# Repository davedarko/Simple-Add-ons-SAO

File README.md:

# Simple-Add-ons-SAO
Hardware Conference Badges tend to turn very complex, so to allow people to add bling and memes to their badge, the SAO (then shitty add-on) standard was developed. It started as a 2x2 header with two power pins and two I2C pins for data and a clock signal. Let me introduce you to the standard and show you what can be achieved. This is one of my favorite things to design, as they can be nice little gifts and inspires a lot of people for future years to also design and gift some. 

They are perfect gifts and spark joy!

Find all of my ~~shitty~~ simple add-ons in this repository. Plus some badges that were never converted to SAO but they still blink and everything.

## The current header - V1.69bis
The header was expanded to a 2x3 ISP connector later. Looking at the simple add-on, this is the layout.

## Designs in this repository

|Badge Name| Type | Eagle | Kicad | Description |
|----------|------|-------|-------|-------------|
| Ghibli/Soot Sprites | SAO | yes | - | A susuwatari simple add-on |
| LECCO postcard  | SAO | yes | - | Reminder token for a good time at Hackaday Europe 2026 in Lecco, Italy |
| Han SAOlo in carbonyte  | SAO | - | yes | work in progress, Attiny202 with RGB LEDs https://hackaday.io/project/197803-han-saolo|
| COVID-19 badge | SAO | - | yes | blinks with the help of a 555 timer on the back https://hackaday.io/project/187615-covid-19-sao-simple-add-on |
| "Hello my name is"  | SAO | - | yes | some blinks, some no https://hackaday.io/project/197693-hello-my-name-is-sao |
| MrAnderson  | SAO | - | yes | work in progress, hommage to Andy Anderson |
| Vendetta badge | SAO | - | yes | "remember, remember the 5th of November" - or anything else with the help of the little EEPROM on the back of this badge |
| Mr. Robot | SAO | yes | yes | with Attiny speaker https://hackaday.io/project/168037-mr-robot-shitty-addon |
| Penghito Poco | SAO | yes | - | small penghicorn badge |
| Do Or Donut | SAO | yes | - |  LED sprinkle matrix https://hackaday.io/project/168597-do-or-donut-sao |
| Knight Rider badge | SAO / pin | yes | yes | K.I.T.T. with animations thanks to an Attiny13 https://hackaday.io/project/25944-kitt-knight-rider-badgebrooch |
| sloth badge | pin | yes | - | inspired by some cute pimoroni pins, a sloth badge was formed https://hackaday.io/project/28330-sloth-badge |
| flux capacitor | pin | yes | - | with animations thanks to an Attiny13, the flux is flowing https://hackaday.io/project/25898-flux-capacitor-trinket|
| retro spacehuhn badge | pin | yes | - | RGB LED eyes on an olg Spacehuhn logo, with markers used for multicolor PCBs https://hackaday.io/project/33886-spacehuhn-badge |
| library stick  | other | yes | - | show off all your simple add-ons |

## Further designs

|Badge Name| Type | Eagle | Kicad | Description |
|----------|------|-------|-------|-------------|
| YoDawgSAO | SAO| - | yes| I heard you like badges on your badges? Here have some badges for your badges for your badges! https://github.com/davedarko/YoDawgSAO |
| T.A.R.S. | SAO| - | yes| Probably my most complex design, a small TARS with display and RP2040 https://github.com/davedarko/TARS-SAO |

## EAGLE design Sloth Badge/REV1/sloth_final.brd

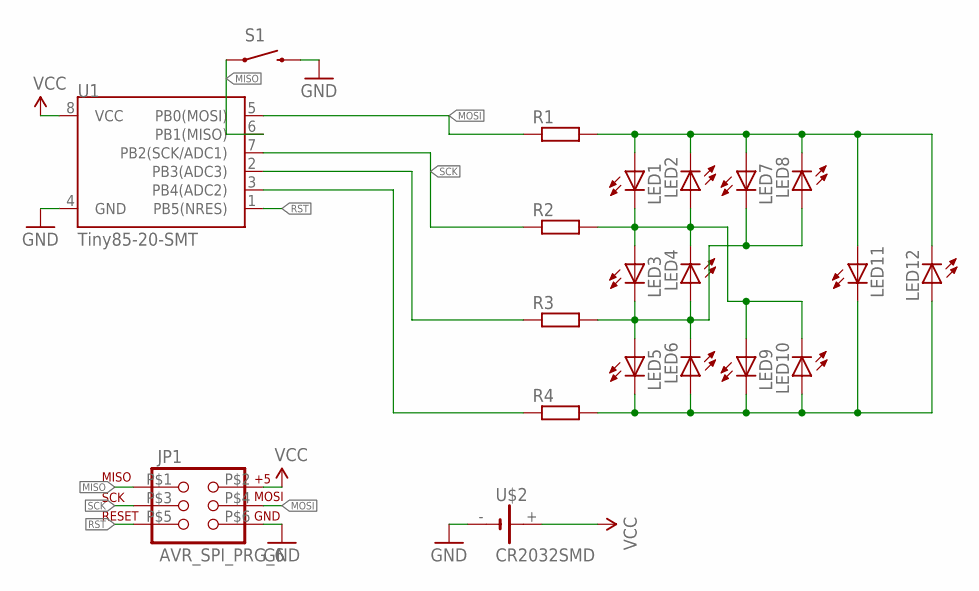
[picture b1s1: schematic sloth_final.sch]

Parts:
JP1: AVR_SPI_PRG_6; 2X3_SMD_PAD
LED1, LED2, LED3, LED4, LED5, LED6, LED7, LED8, LED9, LED10, LED11, LED12: LEDCHIP-LED0805; CHIP-LED0805
R1, R2, R3, R4: R-EU_R0805; R0805
S1: SWITCH-MOMENTARY-2-SMD-1101NE; TACTILE-SWITCH-1101NE
U1: Tiny85-20-SMT; SO08-EIAJ
U$2: CR2032SMD

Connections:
GND: JP1.P$6 (6), S1.P$2 (2), U1.4 (GND), U$2.-
MISO: JP1.P$1 (1), S1.P$1 (1), U1.6 (PB1(MISO))
MOSI: JP1.P$4 (4), R1.1, U1.5 (PB0(MOSI))
unnamed: R4.1, U1.3 (PB4(ADC2))
unnamed: LED5.C, LED6.A, LED9.C, LED10.A, LED11.C, LED12.A, R4.2
unnamed: LED1.A, LED2.C, LED7.A, LED8.C, LED11.A, LED12.C, R1.2
unnamed: LED1.C, LED2.A, LED3.A, LED4.C, LED9.A, LED10.C, R2.2
unnamed: LED3.C, LED4.A, LED5.A, LED6.C, LED7.C, LED8.A, R3.2
PB3: R3.1, U1.2 (PB3(ADC3))
RST: JP1.P$5 (5), U1.1 (PB5(NRES))
SCK: JP1.P$3 (3), R2.1, U1.7 (PB2(SCK/ADC1))
VCC: JP1.P$2 (2), U1.8 (VCC), U$2.+

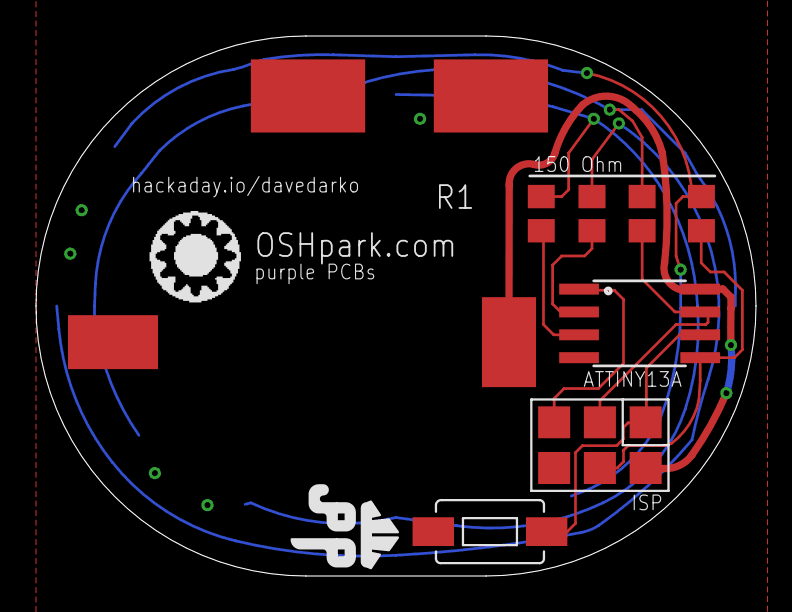
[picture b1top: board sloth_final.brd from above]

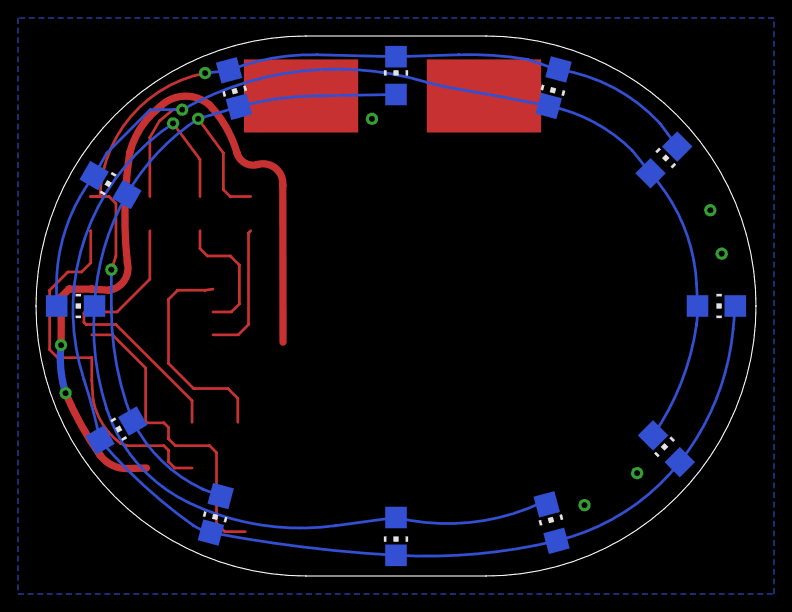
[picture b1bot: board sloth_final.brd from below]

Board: 2 copper layers, 40.0 x 30.0 mm, 22 parts (12 on the bottom side), 12 nets.

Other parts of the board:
U$1: DAVEDARKO2_LOGO
U$3: OSHPARK_LOGO

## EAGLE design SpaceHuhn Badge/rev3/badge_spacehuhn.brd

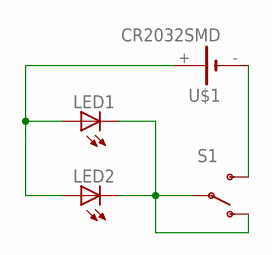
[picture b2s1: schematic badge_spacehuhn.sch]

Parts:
LED1, LED2: LED5MM
S1: SWITCH-SPDT-SMD-A; SWITCH-SPST-SMD-A
U$1: CR2032SMD

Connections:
GND: LED1.K (C), LED2.K (C), S1.1 (O), S1.2
unnamed: S1.3 (S), U$1.-
VCC: LED1.A, LED2.A, U$1.+

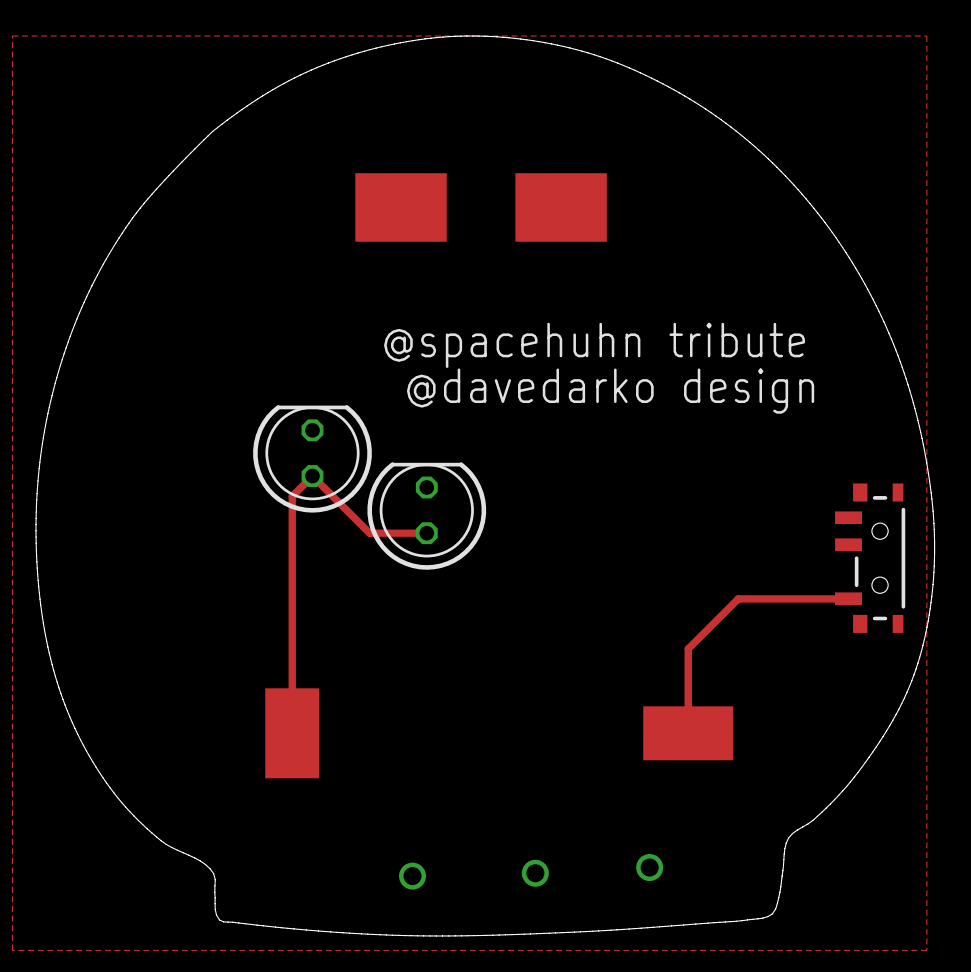
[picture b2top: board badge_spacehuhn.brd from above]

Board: 2 copper layers, 49.9 x 50.0 mm, 5 parts (0 on the bottom side), 3 nets.

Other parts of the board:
U$2: DAVEDARKO_GOLD

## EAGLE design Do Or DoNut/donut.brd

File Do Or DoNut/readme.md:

# Do or Donut SAO
donut shaped LED matrix SAO

## idea
Use an IS31FL3731 to control 8 x 18 LEDs wrapped around a donut shaped PCB, sprinkled with LEDs.

## Links 
- Hackaday IO project page  
[https://hackaday.io/project/168597-do-or-donut-sao](https://hackaday.io/project/168597-do-or-donut-sao)

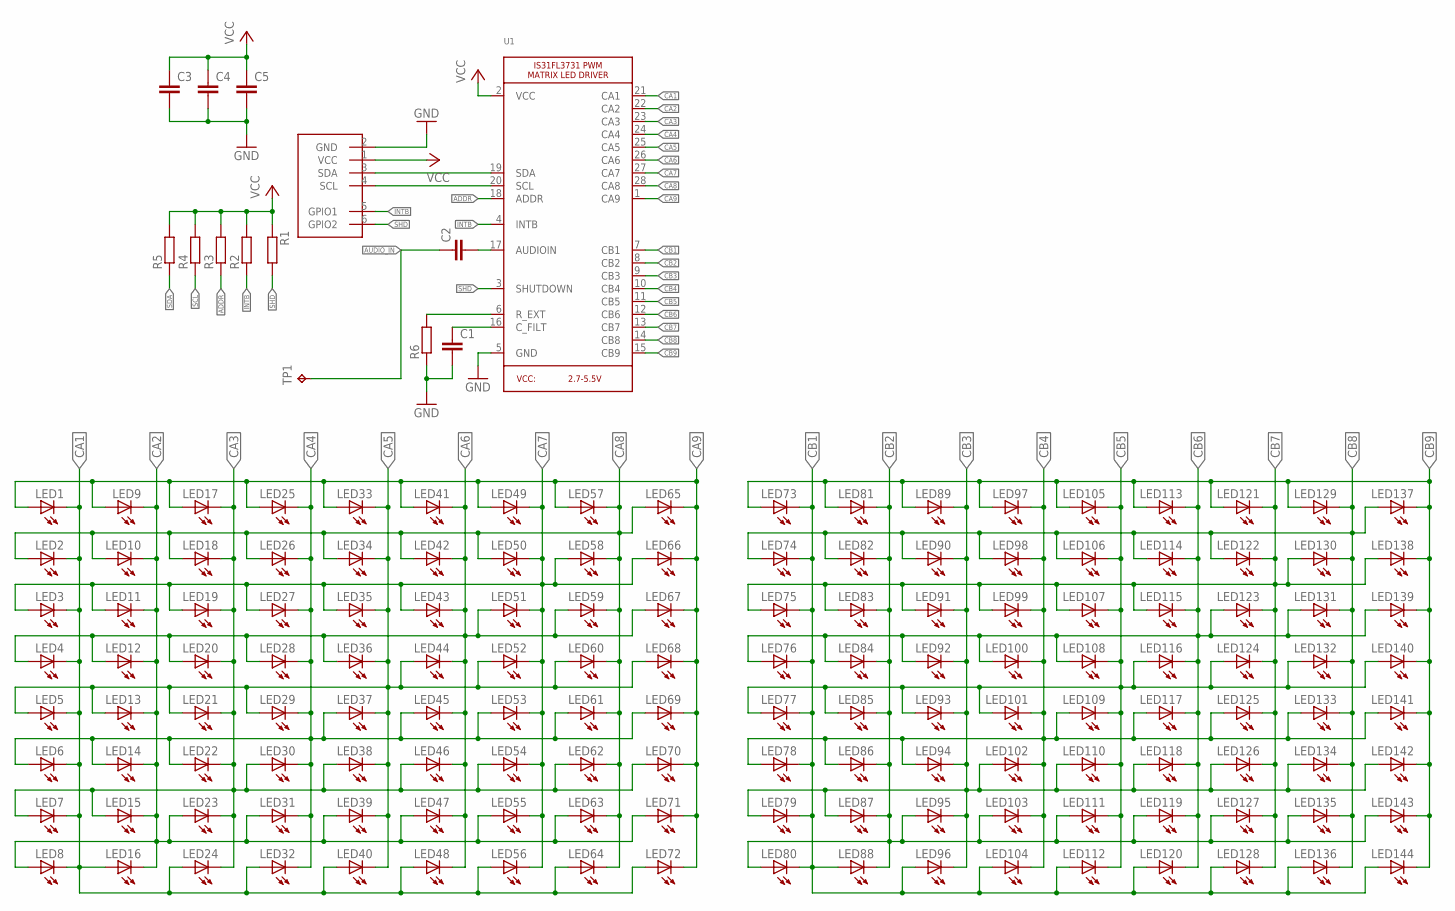
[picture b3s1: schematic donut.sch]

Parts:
C1, C2, C3, C4, C5: C-EUC0603; C0603
LED1, LED2, LED3, LED4, LED5, LED6, LED7, LED8, LED9, LED10, LED11, LED12, LED13, LED14, LED15, LED16, LED17, LED18, LED19, LED20, LED21, LED22, LED23, LED24, LED25, LED26, LED27, LED28, LED29, LED30, LED31, LED32, LED33, LED34, LED35, LED36, LED37, LED38, LED39, LED40, LED41, LED42, LED43, LED44, LED45, LED46, LED47, LED48, LED49, LED50, LED51, LED52, LED53, LED54, LED55, LED56, LED57, LED58, LED59, LED60, LED61, LED62, LED63, LED64, LED65, LED66, LED67, LED68, LED69, LED70, LED71, LED72, LED73, LED74, LED75, LED76, LED77, LED78, LED79, LED80, LED81, LED82, LED83, LED84, LED85, LED86, LED87, LED88, LED89, LED90, LED91, LED92, LED93, LED94, LED95, LED96, LED97, LED98, LED99, LED100, LED101, LED102, LED103, LED104, LED105, LED106, LED107, LED108, LED109, LED110, LED111, LED112, LED113, LED114, LED115, LED116, LED117, LED118, LED119, LED120, LED121, LED122, LED123, LED124, LED125, LED126, LED127, LED128, LED129, LED130, LED131, LED132, LED133, LED134, LED135, LED136, LED137, LED138, LED139, LED140, LED141, LED142, LED143, LED144: LEDCHIP-LED0603; CHIP-LED0603
R1, R2, R3, R4, R5, R6: R-EU_R0603; R0603
TP1: TPB1,27; B1,27
U1: IS31FL3731SSOP; SSOP28DB
U$1: SAO-SHITTY-ADDONBADGE; 2X3-SHROUDED

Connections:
ADDR: R3.1, U1.18 (ADDR)
AIN: C2.2, U1.17 (AUDIOIN)
AUDIO_IN: C2.1, TP1.TP
CA1: LED1.C, LED2.C, LED3.C, LED4.C, LED5.C, LED6.C, LED7.C, LED8.C, LED16.A, LED24.A, LED32.A, LED40.A, LED48.A, LED56.A, LED64.A, LED72.A, U1.21 (CA1)
CA2: LED8.A, LED9.C, LED10.C, LED11.C, LED12.C, LED13.C, LED14.C, LED15.C, LED16.C, LED23.A, LED31.A, LED39.A, LED47.A, LED55.A, LED63.A, LED71.A, U1.22 (CA2)
CA3: LED7.A, LED15.A, LED17.C, LED18.C, LED19.C, LED20.C, LED21.C, LED22.C, LED23.C, LED24.C, LED30.A, LED38.A, LED46.A, LED54.A, LED62.A, LED70.A, U1.23 (CA3)
CA4: LED6.A, LED14.A, LED22.A, LED25.C, LED26.C, LED27.C, LED28.C, LED29.C, LED30.C, LED31.C, LED32.C, LED37.A, LED45.A, LED53.A, LED61.A, LED69.A, U1.24 (CA4)
CA5: LED5.A, LED13.A, LED21.A, LED29.A, LED33.C, LED34.C, LED35.C, LED36.C, LED37.C, LED38.C, LED39.C, LED40.C, LED44.A, LED52.A, LED60.A, LED68.A, U1.25 (CA5)
CA6: LED4.A, LED12.A, LED20.A, LED28.A, LED36.A, LED41.C, LED42.C, LED43.C, LED44.C, LED45.C, LED46.C, LED47.C, LED48.C, LED51.A, LED59.A, LED67.A, U1.26 (CA6)
CA7: LED3.A, LED11.A, LED19.A, LED27.A, LED35.A, LED43.A, LED49.C, LED50.C, LED51.C, LED52.C, LED53.C, LED54.C, LED55.C, LED56.C, LED58.A, LED66.A, U1.27 (CA7)
CA8: LED2.A, LED10.A, LED18.A, LED26.A, LED34.A, LED42.A, LED50.A, LED57.C, LED58.C, LED59.C, LED60.C, LED61.C, LED62.C, LED63.C, LED64.C, LED65.A, U1.28 (CA8)
CA9: LED1.A, LED9.A, LED17.A, LED25.A, LED33.A, LED41.A, LED49.A, LED57.A, LED65.C, LED66.C, LED67.C, LED68.C, LED69.C, LED70.C, LED71.C, LED72.C, U1.1 (CA9)
CB1: LED73.C, LED74.C, LED75.C, LED76.C, LED77.C, LED78.C, LED79.C, LED80.C, LED88.A, LED96.A, LED104.A, LED112.A, LED120.A, LED128.A, LED136.A, LED144.A, U1.7 (CB1)
CB2: LED80.A, LED81.C, LED82.C, LED83.C, LED84.C, LED85.C, LED86.C, LED87.C, LED88.C, LED95.A, LED103.A, LED111.A, LED119.A, LED127.A, LED135.A, LED143.A, U1.8 (CB2)
CB3: LED79.A, LED87.A, LED89.C, LED90.C, LED91.C, LED92.C, LED93.C, LED94.C, LED95.C, LED96.C, LED102.A, LED110.A, LED118.A, LED126.A, LED134.A, LED142.A, U1.9 (CB3)
CB4: LED78.A, LED86.A, LED94.A, LED97.C, LED98.C, LED99.C, LED100.C, LED101.C, LED102.C, LED103.C, LED104.C, LED109.A, LED117.A, LED125.A, LED133.A, LED141.A, U1.10 (CB4)
CB5: LED77.A, LED85.A, LED93.A, LED101.A, LED105.C, LED106.C, LED107.C, LED108.C, LED109.C, LED110.C, LED111.C, LED112.C, LED116.A, LED124.A, LED132.A, LED140.A, U1.11 (CB5)
CB6: LED76.A, LED84.A, LED92.A, LED100.A, LED108.A, LED113.C, LED114.C, LED115.C, LED116.C, LED117.C, LED118.C, LED119.C, LED120.C, LED123.A, LED131.A, LED139.A, U1.12 (CB6)
CB7: LED75.A, LED83.A, LED91.A, LED99.A, LED107.A, LED115.A, LED121.C, LED122.C, LED123.C, LED124.C, LED125.C, LED126.C, LED127.C, LED128.C, LED130.A, LED138.A, U1.13 (CB7)
CB8: LED74.A, LED82.A, LED90.A, LED98.A, LED106.A, LED114.A, LED122.A, LED129.C, LED130.C, LED131.C, LED132.C, LED133.C, LED134.C, LED135.C, LED136.C, LED137.A, U1.14 (CB8)
CB9: LED73.A, LED81.A, LED89.A, LED97.A, LED105.A, LED113.A, LED121.A, LED129.A, LED137.C, LED138.C, LED139.C, LED140.C, LED141.C, LED142.C, LED143.C, LED144.C, U1.15 (CB9)
GND: C1.2, C3.2, C4.2, C5.2, R6.1, U1.5 (GND), U$1.2 (GND)
INTB: R2.1, U1.4 (INTB), U$1.5 (GPIO1)
unnamed: R6.2, U1.6 (R_EXT)
unnamed: C1.1, U1.16 (C_FILT)
SCL: R4.1, U1.20 (SCL), U$1.4 (SCL)
SDA: R5.1, U1.19 (SDA), U$1.3 (SDA)
SHD: R1.2, U1.3 (SHUTDOWN), U$1.6 (GPIO2)
VCC: C3.1, C4.1, C5.1, R1.1, R2.2, R3.2, R4.2, R5.2, U1.2 (VCC), U$1.1 (VCC)

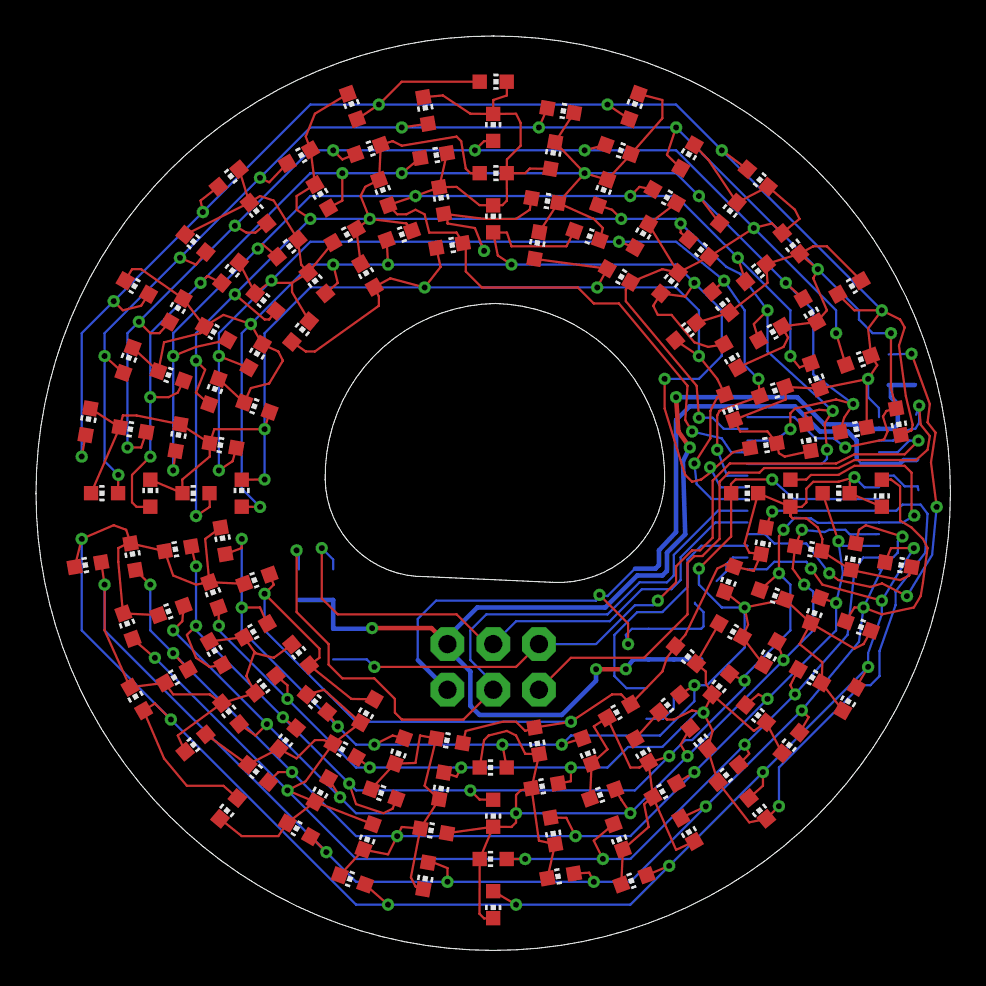
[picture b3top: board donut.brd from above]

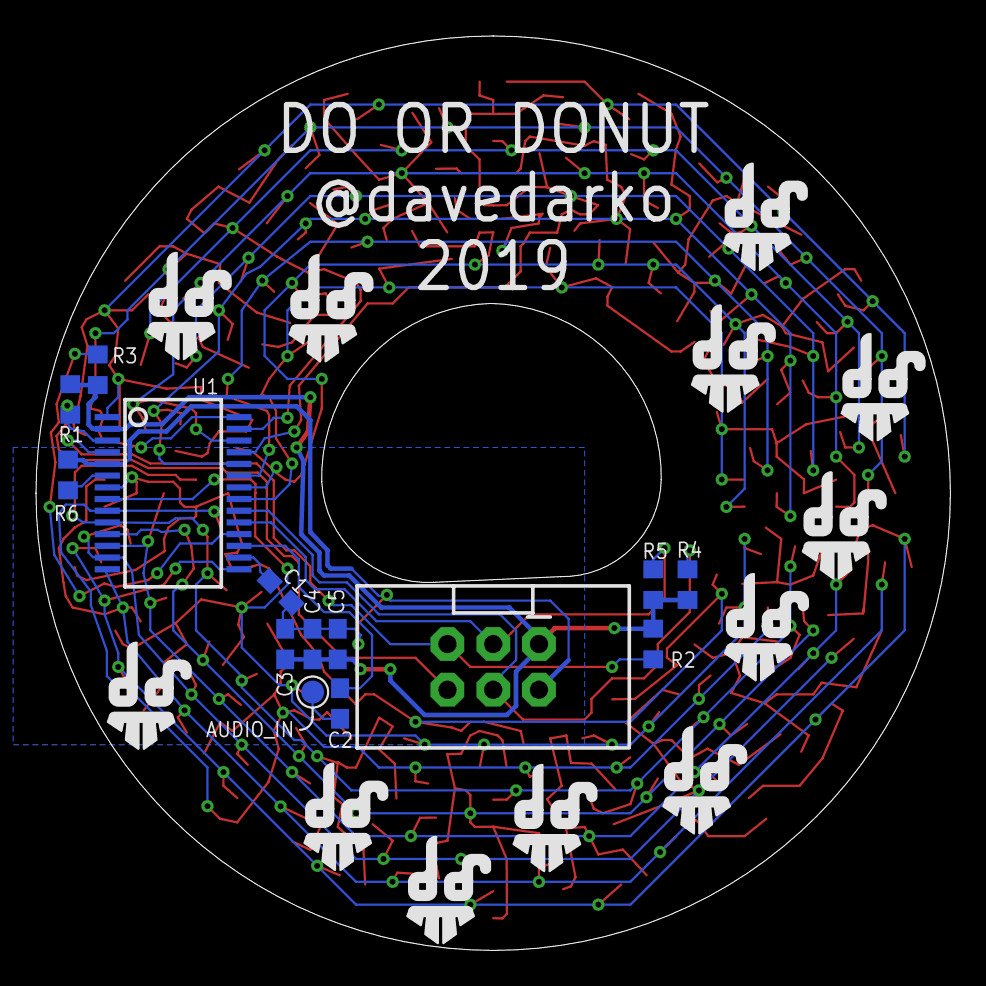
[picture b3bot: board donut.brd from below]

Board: 2 copper layers, 50.8 x 50.8 mm, 170 parts (26 on the bottom side), 29 nets.

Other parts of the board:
U$2, U$3, U$4, U$5, U$6, U$7, U$8, U$9, U$10, U$11, U$12, U$13: DAVEDARKO2_LOGO

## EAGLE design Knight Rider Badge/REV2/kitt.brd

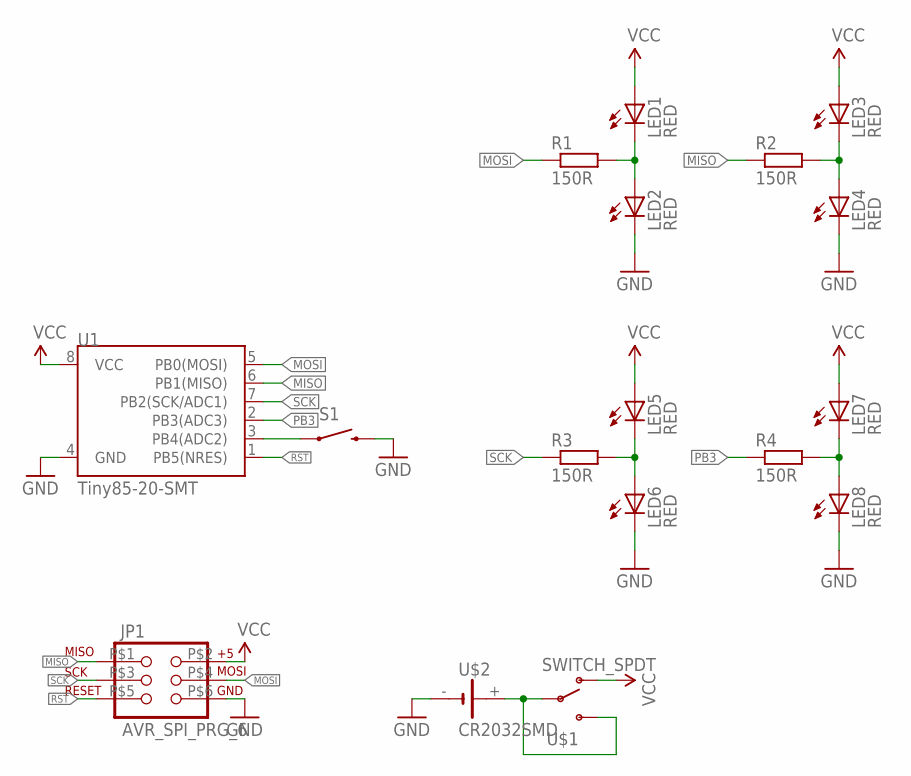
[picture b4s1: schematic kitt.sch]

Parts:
JP1: AVR_SPI_PRG_6; 2X3_SMD_PAD
LED1, LED2, LED3, LED4, LED5, LED6, LED7, LED8: RED; CHIP-LED0805
R1, R2, R3, R4: 150R; M0805
S1: SWITCH-MOMENTARY-2-SMD-1101NE; TACTILE-SWITCH-1101NE
U1: Tiny85-20-SMT; SO08-EIAJ
U$1: SWITCH_SPDT; KPS-1290
U$2: CR2032SMD

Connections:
GND: JP1.P$6 (6), LED2.C, LED4.C, LED6.C, LED8.C, S1.P$2 (2), U1.4 (GND), U$2.-
MISO: JP1.P$1 (1), R2.1, U1.6 (PB1(MISO))
MOSI: JP1.P$4 (4), R1.1, U1.5 (PB0(MOSI))
unnamed: S1.P$1 (1), U1.3 (PB4(ADC2))
unnamed: LED1.C, LED2.A, R1.2
unnamed: U$1.P, U$1.S, U$2.+
unnamed: LED3.C, LED4.A, R2.2
unnamed: LED5.C, LED6.A, R3.2
unnamed: LED7.C, LED8.A, R4.2
PB3: R4.1, U1.2 (PB3(ADC3))
RST: JP1.P$5 (5), U1.1 (PB5(NRES))
SCK: JP1.P$3 (3), R3.1, U1.7 (PB2(SCK/ADC1))
VCC: JP1.P$2 (2), LED1.A, LED3.A, LED5.A, LED7.A, U1.8 (VCC), U$1.O

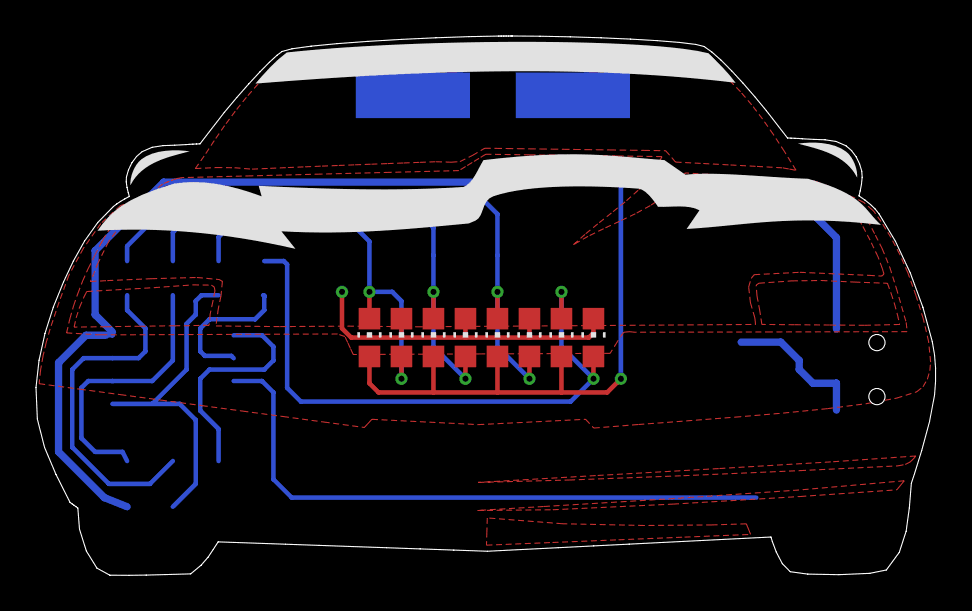
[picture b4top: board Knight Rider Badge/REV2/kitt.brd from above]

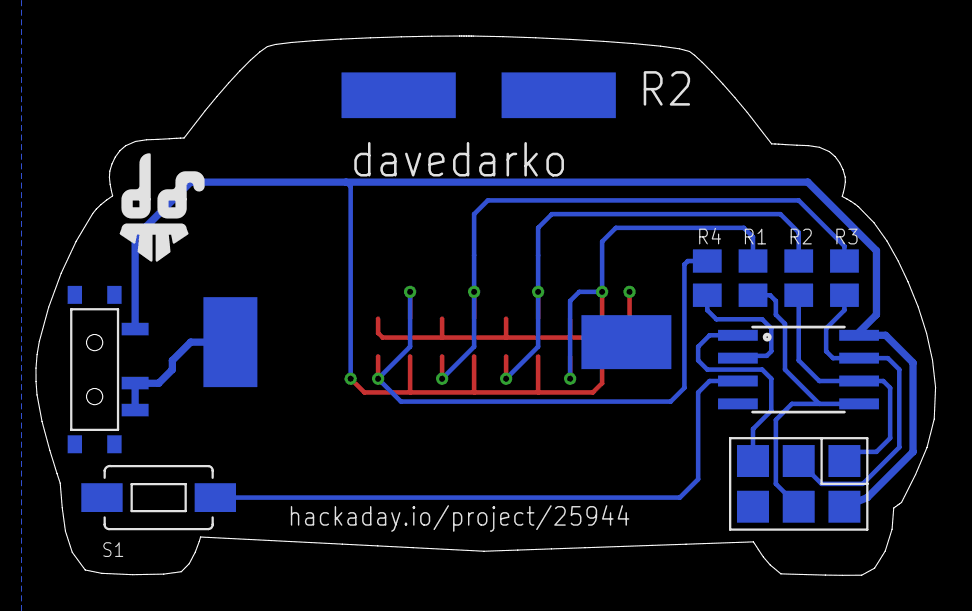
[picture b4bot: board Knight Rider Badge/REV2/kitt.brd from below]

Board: 2 copper layers, 50.0 x 30.0 mm, 18 parts (10 on the bottom side), 13 nets.

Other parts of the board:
U$3: DAVEDARKO2_LOGO

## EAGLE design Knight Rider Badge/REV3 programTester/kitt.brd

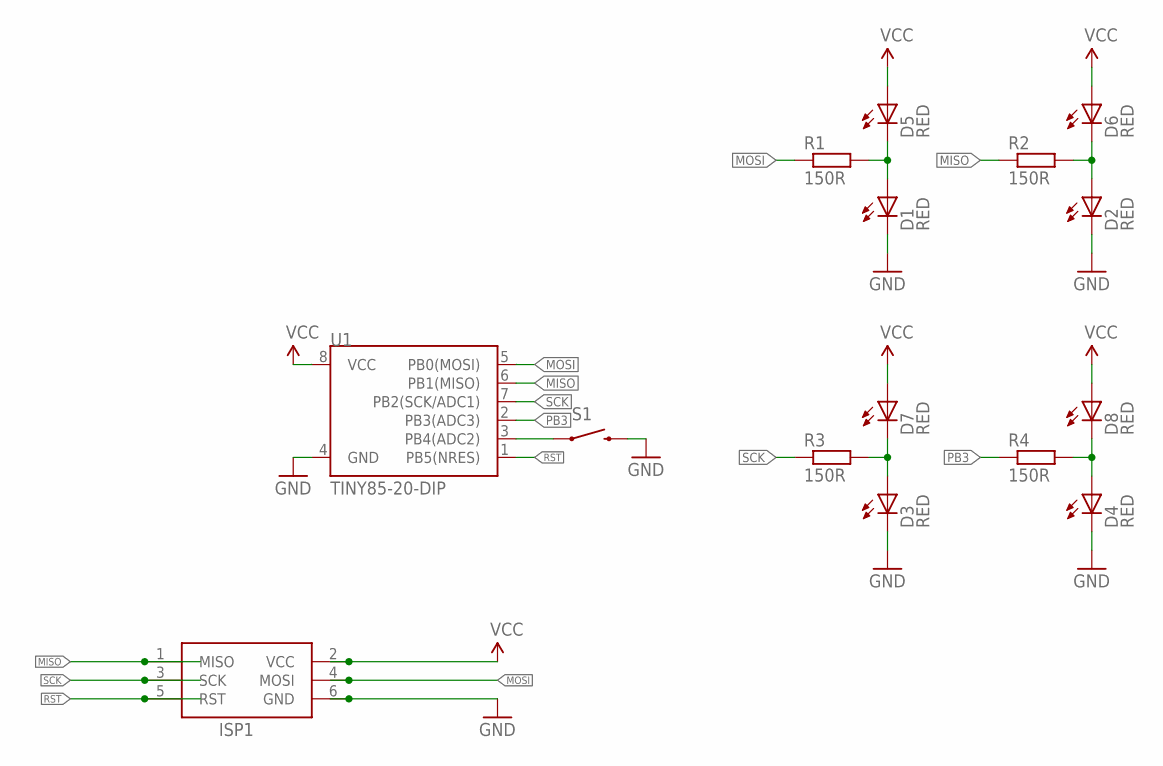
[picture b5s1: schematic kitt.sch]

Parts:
D1, D2, D3, D4, D5, D6, D7, D8: RED; CHIP-LED0805
ISP1: AVRISP-BOX
R1, R2, R3, R4: 150R; M0805
S1: SWITCH-MOMENTARY-2PTH; TACTILE-PTH
U1: TINY85-20-DIP; DIP08

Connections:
GND: D1.C, D2.C, D3.C, D4.C, ISP1.6 (GND), S1.3 (2), U1.4 (GND)
MISO: ISP1.1 (MISO), R2.1, U1.6 (PB1(MISO))
MOSI: ISP1.4 (MOSI), R1.1, U1.5 (PB0(MOSI))
unnamed: S1.1, U1.3 (PB4(ADC2))
unnamed: D1.A, D5.C, R1.2
unnamed: D2.A, D6.C, R2.2
unnamed: D3.A, D7.C, R3.2
unnamed: D4.A, D8.C, R4.2
PB3: R4.1, U1.2 (PB3(ADC3))
RST: ISP1.5 (RST), U1.1 (PB5(NRES))
SCK: ISP1.3 (SCK), R3.1, U1.7 (PB2(SCK/ADC1))
VCC: D5.A, D6.A, D7.A, D8.A, ISP1.2 (VCC), U1.8 (VCC)

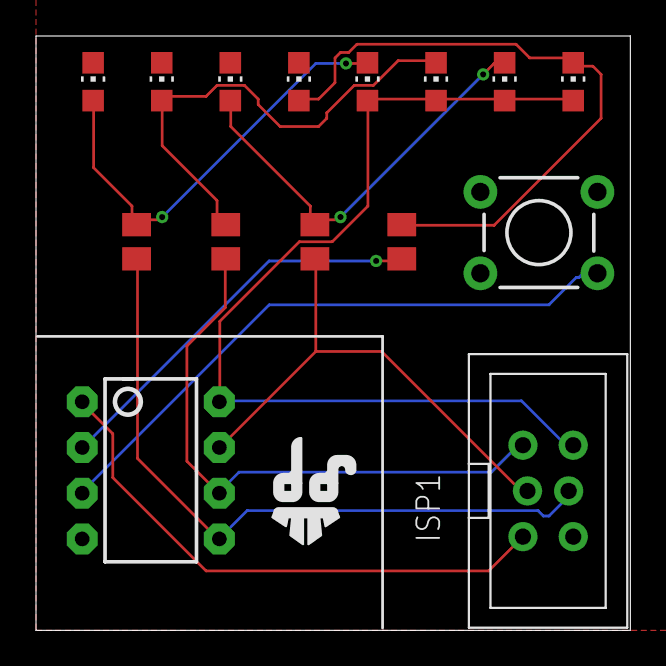
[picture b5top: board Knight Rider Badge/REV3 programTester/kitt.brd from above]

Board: 2 copper layers, 33.0 x 33.0 mm, 16 parts (0 on the bottom side), 12 nets.

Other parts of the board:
U$3: DAVEDARKO2_LOGO

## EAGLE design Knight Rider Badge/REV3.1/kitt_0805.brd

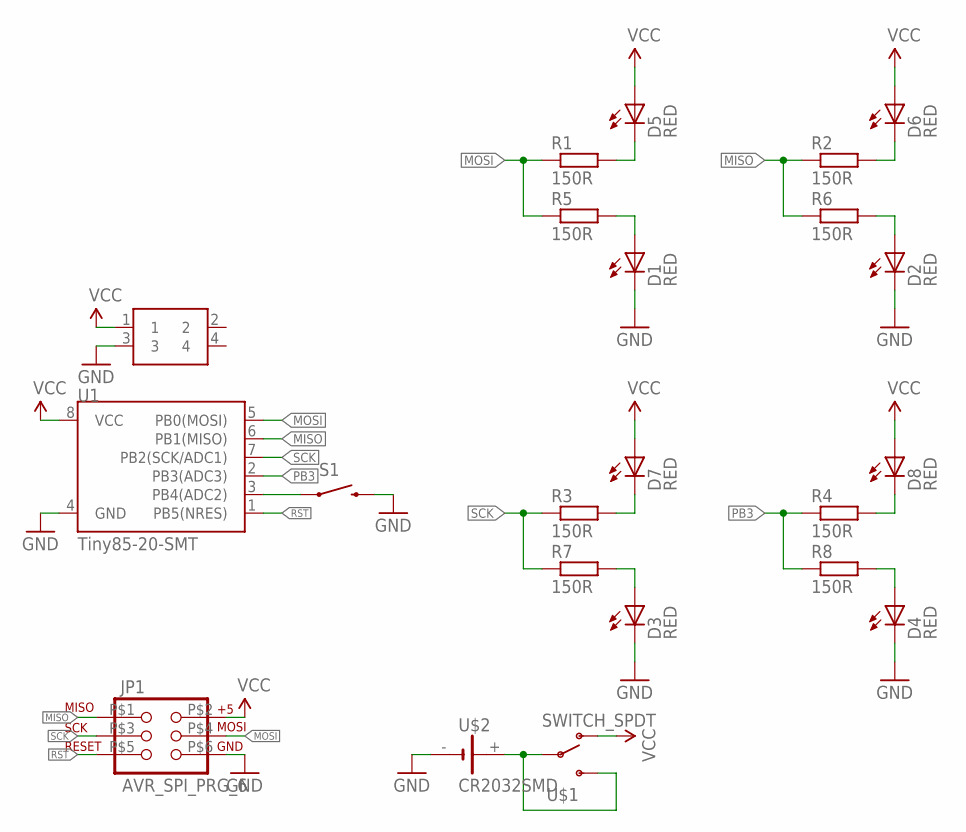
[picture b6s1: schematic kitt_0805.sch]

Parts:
D1, D2, D3, D4, D5, D6, D7, D8: RED; CHIP-LED0805
JP1: AVR_SPI_PRG_6; 2X3_SMD_PAD
R1, R2, R3, R4, R5, R6, R7, R8: 150R; M0805
S1: SWITCH-MOMENTARY-2-SMD-1101NE; TACTILE-SWITCH-1101NE
U1: Tiny85-20-SMT; SO08-EIAJ
U$1: SWITCH_SPDT; KPS-1290
U$2: CR2032SMD
U$4: 2X2-SMT

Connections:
GND: D1.C, D2.C, D3.C, D4.C, JP1.P$6 (6), S1.P$2 (2), U1.4 (GND), U$2.-, U$4.3
MISO: JP1.P$1 (1), R2.1, R6.1, U1.6 (PB1(MISO))
MOSI: JP1.P$4 (4), R1.1, R5.1, U1.5 (PB0(MOSI))
unnamed: S1.P$1 (1), U1.3 (PB4(ADC2))
unnamed: D5.C, R1.2
unnamed: D1.A, R5.2
unnamed: D3.A, R7.2
unnamed: U$1.P, U$1.S, U$2.+
unnamed: D4.A, R8.2
unnamed: D2.A, R6.2
unnamed: D6.C, R2.2
unnamed: D7.C, R3.2
unnamed: D8.C, R4.2
PB3: R4.1, R8.1, U1.2 (PB3(ADC3))
RST: JP1.P$5 (5), U1.1 (PB5(NRES))
SCK: JP1.P$3 (3), R3.1, R7.1, U1.7 (PB2(SCK/ADC1))
VCC: D5.A, D6.A, D7.A, D8.A, JP1.P$2 (2), U1.8 (VCC), U$1.O, U$4.1

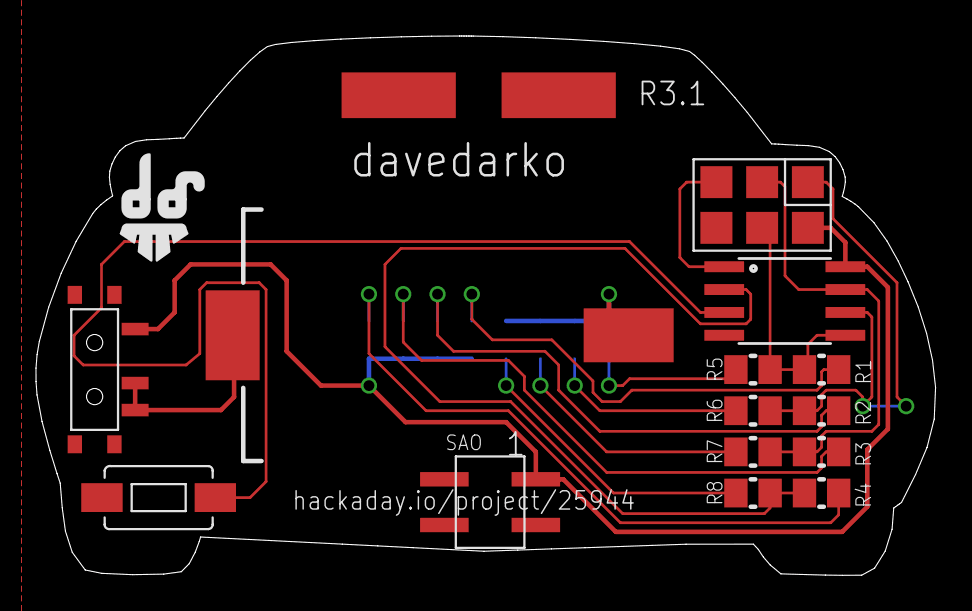
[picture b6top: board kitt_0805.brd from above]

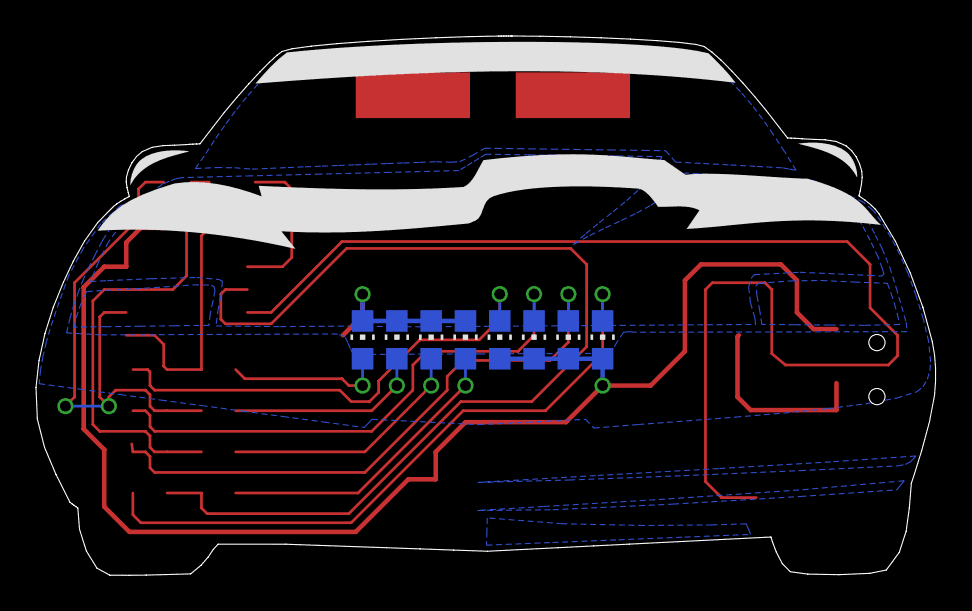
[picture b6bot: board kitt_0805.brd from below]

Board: 2 copper layers, 50.0 x 30.0 mm, 23 parts (8 on the bottom side), 17 nets.

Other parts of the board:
U$3: DAVEDARKO2_LOGO

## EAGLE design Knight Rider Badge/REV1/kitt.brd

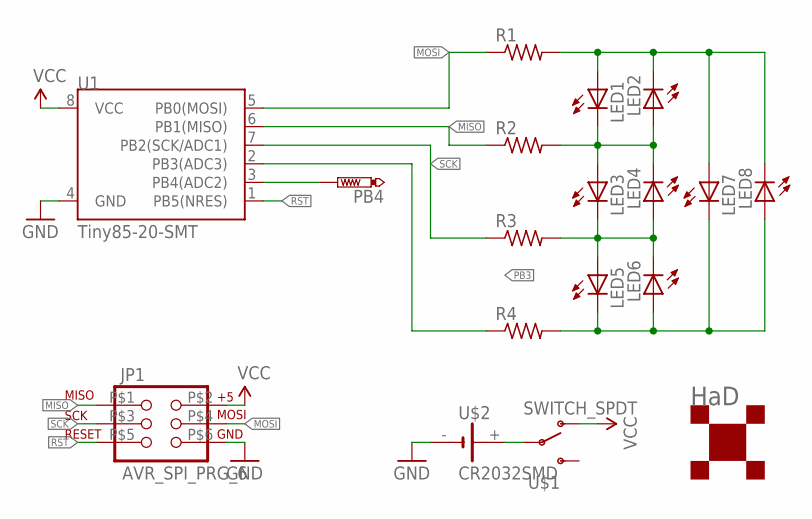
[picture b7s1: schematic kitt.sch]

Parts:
JP1: AVR_SPI_PRG_6; 2X3_SMD_PAD
LED1, LED2, LED3, LED4, LED5, LED6, LED7, LED8: LEDCHIPLED-0603-TTW; CHIPLED-0603-TTW
PB4: PTR1B1,27; B1,27
R1, R2, R3, R4: R-US_R0603; R0603
U1: Tiny85-20-SMT; SO08-EIAJ
U$1: SWITCH_SPDT; KPS-1290
U$2: CR2032SMD
U$3: HACKADAY_1CM; HACKADAY_LOGO

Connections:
MISO: JP1.P$1 (1), R2.1, U1.6 (PB1(MISO))
MOSI: JP1.P$4 (4), R1.1, U1.5 (PB0(MOSI))
unnamed: PB4.TP, U1.3 (PB4(ADC2))
unnamed: U$1.P, U$2.+
unnamed: LED1.A@1 (A), LED2.C@1 (C), LED7.A@1 (A), LED8.C@1 (C), R1.2
unnamed: LED5.C@1 (C), LED6.A@1 (A), LED7.C@1 (C), LED8.A@1 (A), R4.2
unnamed: LED1.C@1 (C), LED2.A@1 (A), LED3.A@1 (A), LED4.C@1 (C), R2.2
unnamed: LED3.C@1 (C), LED4.A@1 (A), LED5.A@1 (A), LED6.C@1 (C), R3.2
unnamed: JP1.P$6 (6), U1.4 (GND), U$2.-
PB3: R4.1, U1.2 (PB3(ADC3))
RST: JP1.P$5 (5), U1.1 (PB5(NRES))
SCK: JP1.P$3 (3), R3.1, U1.7 (PB2(SCK/ADC1))
VCC: JP1.P$2 (2), U1.8 (VCC), U$1.O

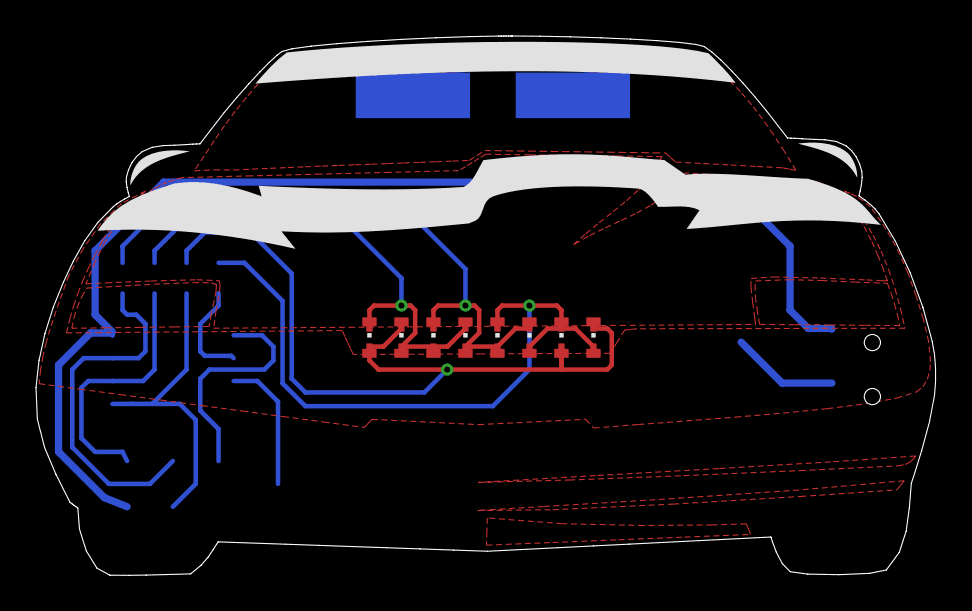
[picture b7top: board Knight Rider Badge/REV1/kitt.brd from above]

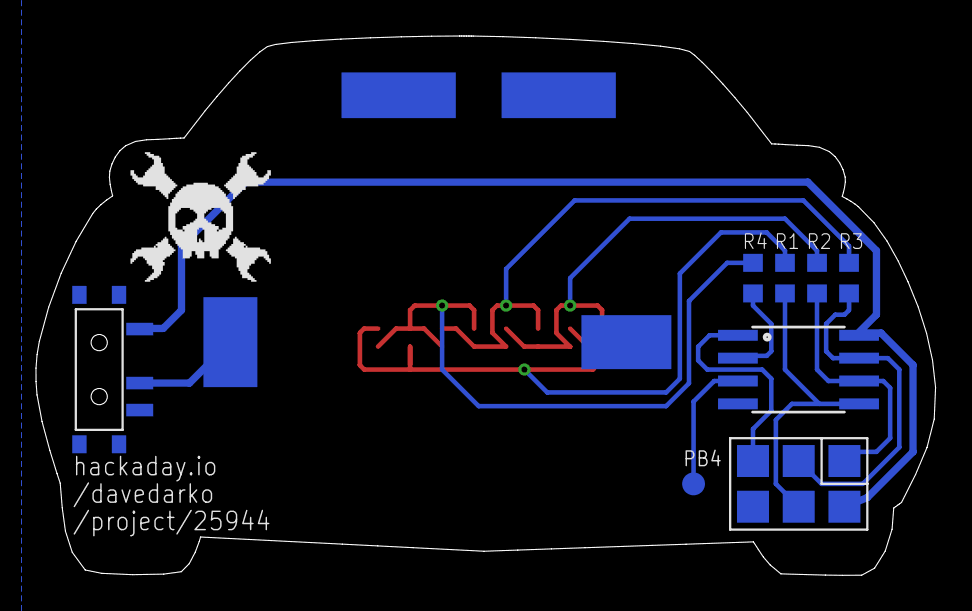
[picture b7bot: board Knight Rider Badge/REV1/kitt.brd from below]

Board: 2 copper layers, 50.0 x 30.0 mm, 18 parts (10 on the bottom side), 13 nets.

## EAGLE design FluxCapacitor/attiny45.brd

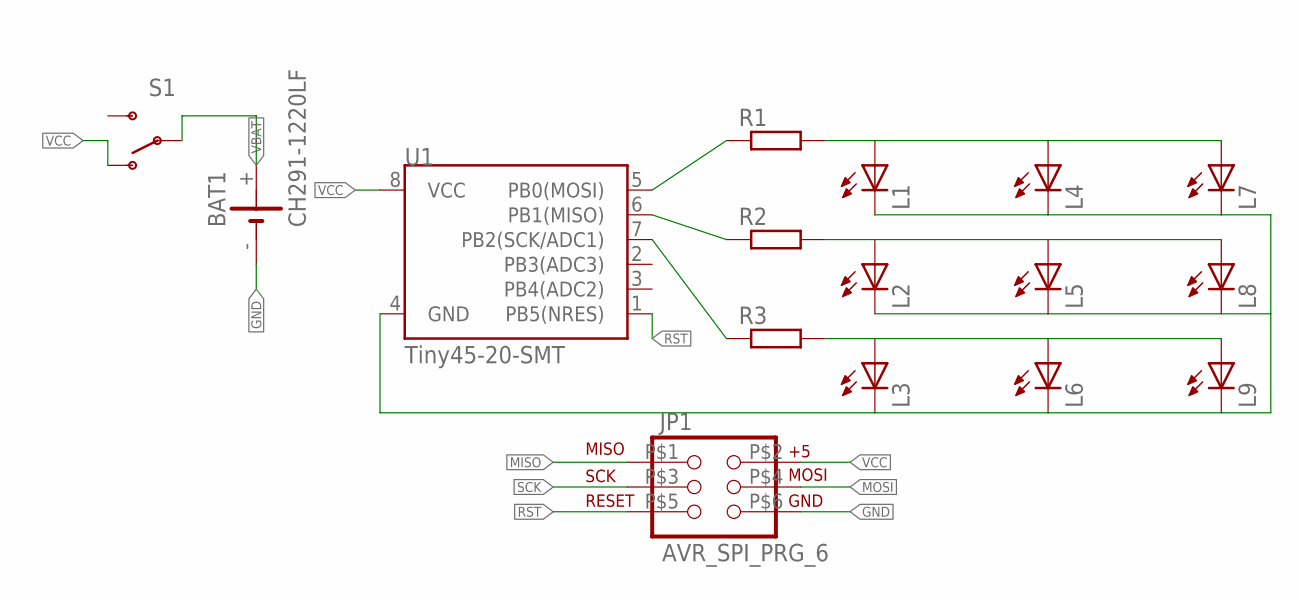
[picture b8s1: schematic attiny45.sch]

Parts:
BAT1: CH291-1220LF
JP1: AVR_SPI_PRG_6; 2X3_SMD_PAD
L1, L2, L3, L4, L5, L6, L7, L8, L9: LEDSML1206; SML1206
R1, R2, R3: R-EU_M0805; M0805
S1: SWITCH-SPDT-SMD-A; SWITCH-SPST-SMD-A
U1: Tiny45-20-SMT; SO08-EIAJ

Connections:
GND: BAT1.-, JP1.P$6 (6), L1.C, L2.C, L3.C, L4.C, L5.C, L6.C, L7.C, L8.C, L9.C, U1.4 (GND)
MISO: JP1.P$1 (1), R2.1, U1.6 (PB1(MISO))
MOSI: JP1.P$4 (4), R1.1, U1.5 (PB0(MOSI))
unnamed: L1.A, L4.A, L7.A, R1.2
unnamed: L2.A, L5.A, L8.A, R2.2
unnamed: L3.A, L6.A, L9.A, R3.2
RST: JP1.P$5 (5), U1.1 (PB5(NRES))
SCK: JP1.P$3 (3), R3.1, U1.7 (PB2(SCK/ADC1))
VBAT: BAT1.+, S1.2
VCC: JP1.P$2 (2), S1.1 (O), U1.8 (VCC)

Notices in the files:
parts and their libraries:
SparkFun-Connectors: Licensing: Creative Commons ShareAlike 4.0 International - https://creativecommons.org/licenses/by-sa/4.0
